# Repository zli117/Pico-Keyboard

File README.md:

# Pico-Keyboard

A hot-swappable mechanical keyboard built from scratch with Pi Pico board, and 3D printed case, with a very configurable firmware. The firmware is in a separate repo: https://github.com/zli117/PicoMK and can be reused for other RP2040 keyboards.

# Pictures

## PCB

## Case

## Build Pictures

# Overall Cost Breakdown

In total per keyboard material cost is roughly $129.57

 * 5 PCB from JLCPCB with shipping: $39.52. Roughly $7.9 per board.
 * 100 hot-swappable PCB socket: $14.50. Used 68, so total $9.86.
 * Pi Pico: $4.99.
 * EC11 Rotary Encoder: $1.10 each.
 * COM-09032 Joystick: $4.50 each.
 * 100 1N4148 diodes: $4.99. Used 70 so $3.50.
 * 150 WS2812B: $14.49. Used 17, so total $1.64.
 * 3D printed case. Each part weight about 50g and there are 5 (2 for plate, and 3 for bottom). Total weight 250g roughly $6.
 * SSD1306 white color: $3 each.
 * GMMK encoder knob: $10.
 * Clear joystick knob: $5.
 * Stabilizers: $16.99 per set.
 * Akko clear translucent keycap: $39.99.
 * Akko blue switch: $9.99 per 45. Used 68, so total $15.10
 
# Build Instructions

## PCB
PCB is designed with KiCAD 6, and everything is under the [PCB](PCB/) folder. Pre-plotted files that can be uploaded to board factory are in 
`Gerber.zip` file. However, different factory may have different plotting settings, so it's recommended to replot with KiCad following factory's instruction. The provided one is for JLCPCB. 

## Case
Case is designed with Fusion 360. The file ends in `.f3z` contains the original Fusion 360 source. My build used SUNLU Clear PLA and is sliced with Cura. I put screw holes on the bottom to secure the PCB, but in practice it's not necessary to screw down the PCB once you've installed switches. So those are optional. The screws between plate and bottom are not optional however.

## Firmware
Firmware is in a separate repo: [PicoMK](https://github.com/zli117/PicoMK). Please see the instruction on how to configure and build the firmware there. 

# PCB Library Licenses

 * Pico symbol, footprint from https://github.com/ncarandini/KiCad-RP-Pico under CC-BY-SA 4.0. 3D model for Pico is obtained from Raspberry Pi Foundation.
 * COM-09032 symbol, footprint and 3D models are from SnapEDA.
 * Key switch footprints and 3D models are from https://github.com/perigoso/keyswitch-kicad-library 
 * Other symbols are from KiCad library which is under CC-BY-SA 4.0 license. 

This work is licensed under a
[Creative Commons Attribution-ShareAlike 4.0 International License][cc-by-sa].

[![CC BY-SA 4.0][cc-by-sa-image]][cc-by-sa]

[cc-by-sa]: http://creativecommons.org/licenses/by-sa/4.0/
[cc-by-sa-image]: https://licensebuttons.net/l/by-sa/4.0/88x31.png
[cc-by-sa-shield]: https://img.shields.io/badge/License-CC%20BY--SA%204.0-lightgrey.svg

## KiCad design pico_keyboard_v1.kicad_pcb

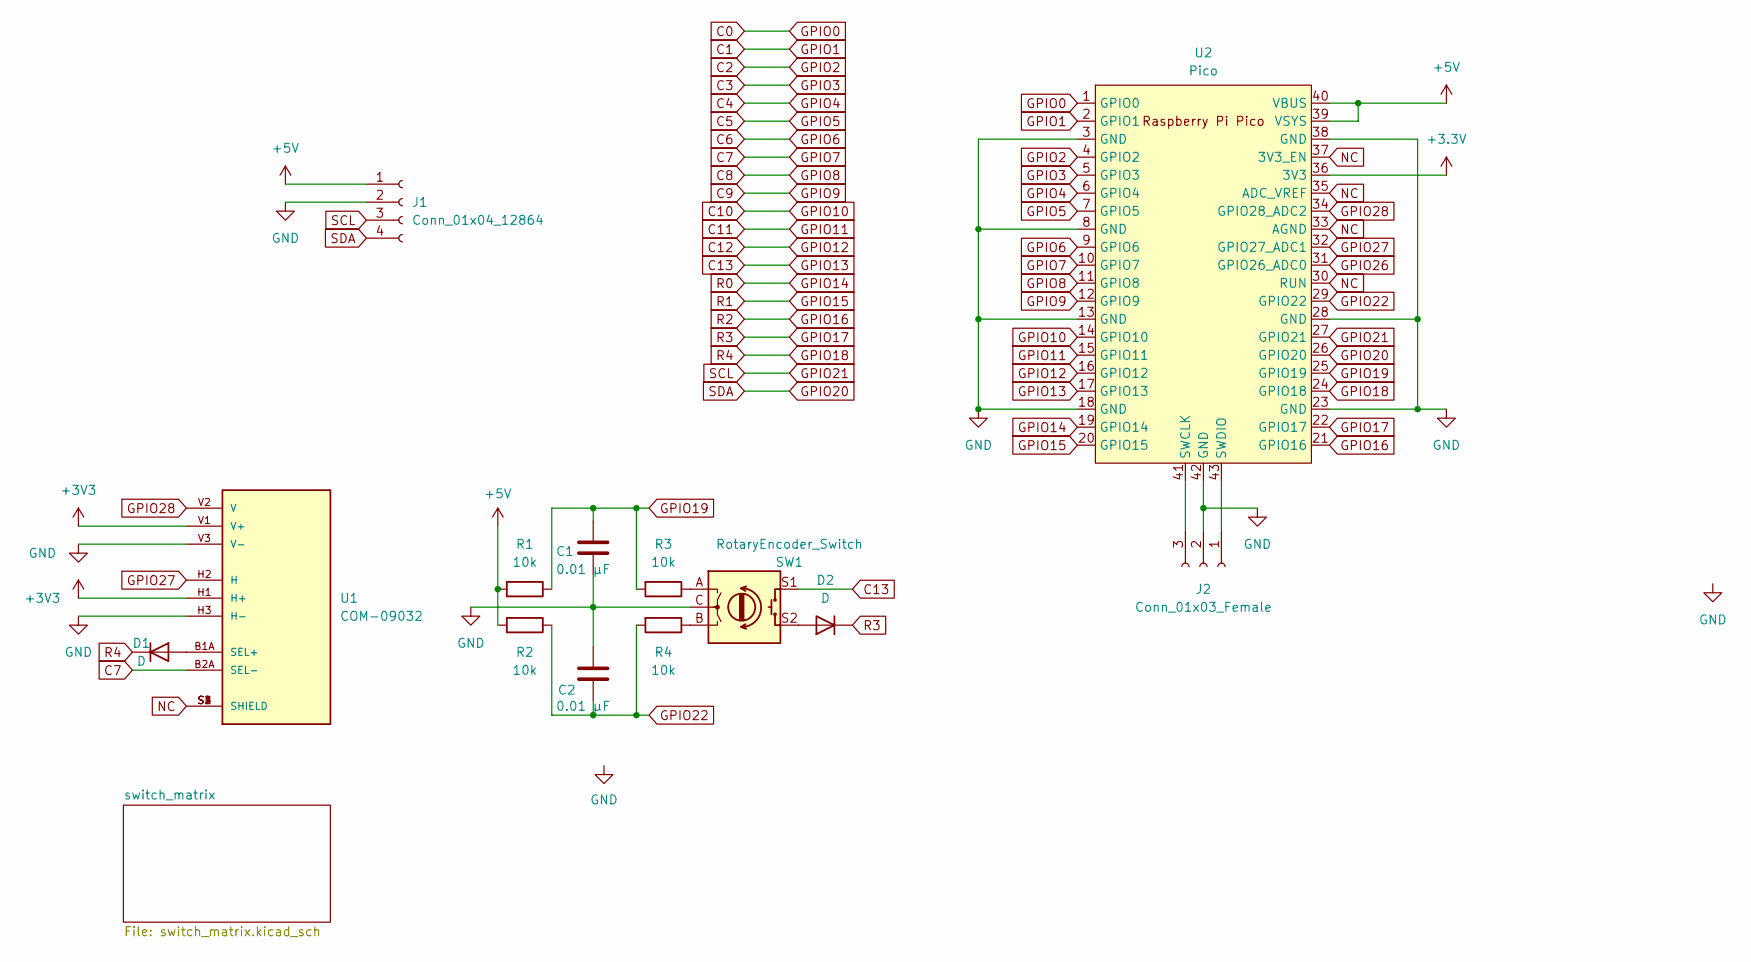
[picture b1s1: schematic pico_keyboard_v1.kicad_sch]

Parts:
C1, C2: 0.01 μF; C_1206_3216Metric_Pad1.33x1.80mm_HandSolder
D1, D2: D; D_DO-35_SOD27_P7.62mm_Horizontal
J1: Conn_01x04_12864; PinHeader_1x04_P2.00mm_Vertical
J2: Conn_01x03_Female; PinHeader_1x03_P2.00mm_Vertical
R1, R2, R3, R4: 10k; R_Axial_DIN0207_L6.3mm_D2.5mm_P10.16mm_Horizontal
SW1: RotaryEncoder_Switch; RotaryEncoder_Alps_EC11E-Switch_Vertical_H20mm_CircularMoun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
U1: COM-09032; XDCR_COM-09032; PARTREV N/A
U2: Pico; RPi_Pico_SMD_TH

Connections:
+5V: J1.1, R1.2, R2.2, U2.39 (VSYS), U2.40 (VBUS)
C0: U2.1 (GPIO0); also elsewhere on the board
C1: U2.2 (GPIO1); also elsewhere on the board
C2: U2.4 (GPIO2); also elsewhere on the board
C3: U2.5 (GPIO3); also elsewhere on the board
C4: U2.6 (GPIO4); also elsewhere on the board
C5: U2.7 (GPIO5); also elsewhere on the board
C6: U2.9 (GPIO6); also elsewhere on the board
C7: U1.B2A (SEL-), U2.10 (GPIO7); also elsewhere on the board
C8: U2.11 (GPIO8); also elsewhere on the board
C9: U2.12 (GPIO9); also elsewhere on the board
C10: U2.14 (GPIO10); also elsewhere on the board
C11: U2.15 (GPIO11); also elsewhere on the board
C12: U2.16 (GPIO12); also elsewhere on the board
C13: SW1.S1, U2.17 (GPIO13); also elsewhere on the board
GND: C1.2, C2.1, J1.2, J2.2, SW1.C, U1.H3 (H-), U1.V3 (V-), U2.3 (GND), U2.8 (GND), U2.13 (GND), U2.18 (GND), U2.23 (GND), U2.28 (GND), U2.38 (GND), U2.42 (GND)
GPIO14: U2.19 (GPIO14); also elsewhere on the board
GPIO15: U2.20 (GPIO15); also elsewhere on the board
GPIO16: U2.21 (GPIO16); also elsewhere on the board
GPIO17: D2.1 (K), U2.22 (GPIO17); also elsewhere on the board
GPIO18: D1.1 (K), U2.24 (GPIO18); also elsewhere on the board
GPIO19: C1.1, R1.1, R3.2, U2.25 (GPIO19)
GPIO20: J1.4, U2.26 (GPIO20)
GPIO21: J1.3, U2.27 (GPIO21)
GPIO22: C2.2, R2.1, R4.2, U2.29 (GPIO22)
GPIO26: U2.31 (GPIO26_ADC0)
GPIO27: U1.H2 (H), U2.32 (GPIO27_ADC1)
GPIO28: U1.V2 (V), U2.34 (GPIO28_ADC2)
NC: U1.S1 (SHIELD), U1.S2 (SHIELD), U1.S3 (SHIELD), U1.S4 (SHIELD), U2.30 (RUN), U2.33 (AGND), U2.35 (ADC_VREF), U2.37 (3V3_EN)
unnamed: D1.2 (A), U1.B1A (SEL+)
unnamed: D2.2 (A), SW1.S2
unnamed: J2.1, U2.43 (SWDIO)
unnamed: J2.3, U2.41 (SWCLK)
unnamed: R3.1, SW1.A
unnamed: R4.1, SW1.B

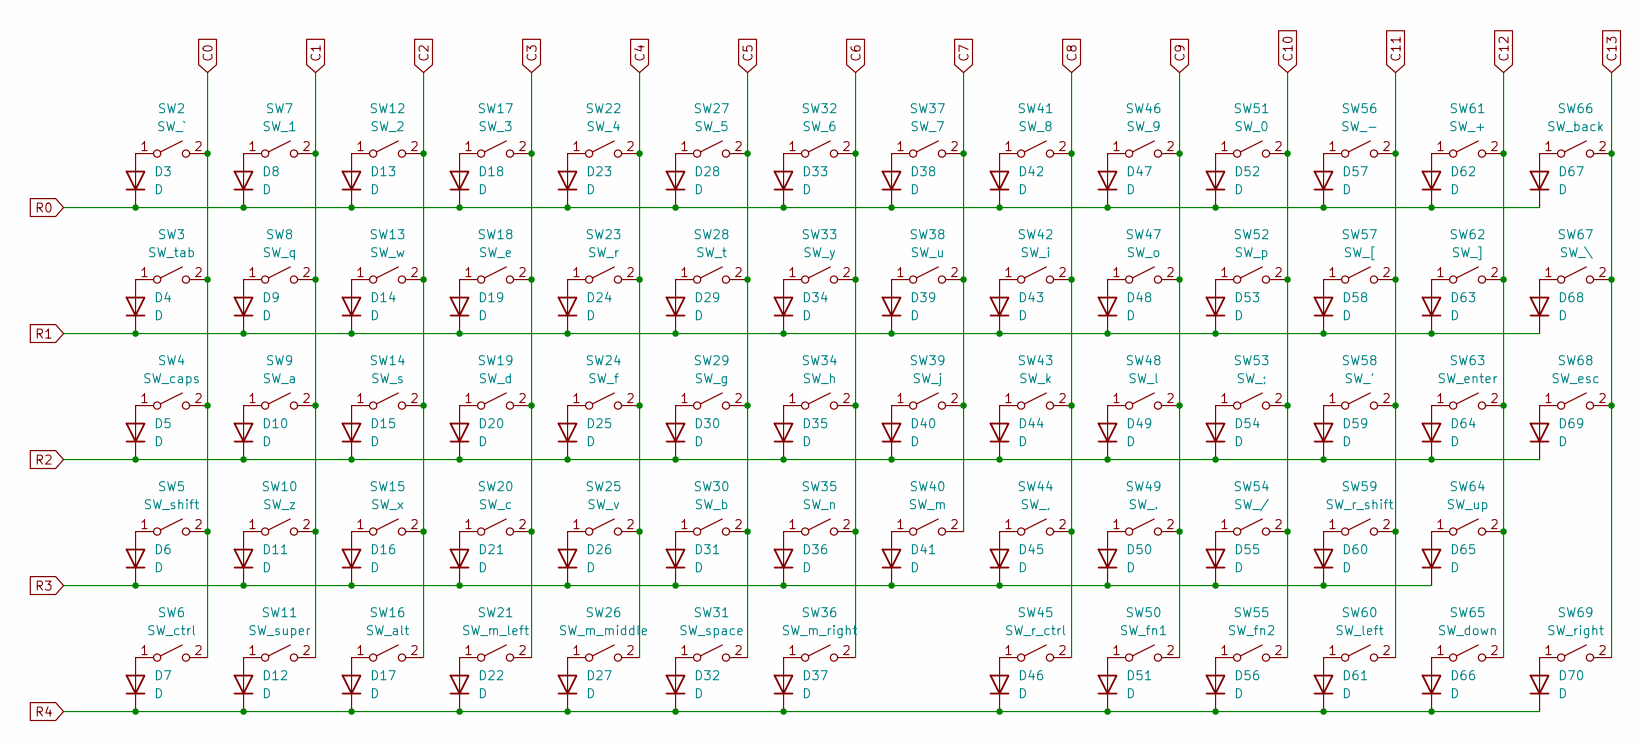
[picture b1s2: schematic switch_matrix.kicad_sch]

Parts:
D3, D4, D5, D6, D7, D8, D9, D10, D11, D12, D13, D14, D15, D16, D17, D18, D19, D20, D21, D22, D23, D24, D25, D26, D27, D28, D29, D30, D31, D32, D33, D34, D35, D36, D37, D38, D39, D40, D41, D42, D43, D44, D45, D46, D47, D48, D49, D50, D51, D52, D53, D54, D55, D56, D57, D58, D59, D60, D61, D62, D63, D64, D65, D66, D67, D68, D69, D70: D; D_DO-35_SOD27_P7.62mm_Horizontal
SW2: SW_`; SW_Hotswap_Kailh_MX_1.00u
SW3: SW_tab; SW_Hotswap_Kailh_MX_1.50u
SW4: SW_caps; SW_Hotswap_Kailh_MX_1.75u
SW5: SW_shift; SW_Hotswap_Kailh_MX_2.25u
SW6: SW_ctrl; SW_Hotswap_Kailh_MX_1.25u
SW7: SW_1; SW_Hotswap_Kailh_MX_1.00u
SW8: SW_q; SW_Hotswap_Kailh_MX_1.00u
SW9: SW_a; SW_Hotswap_Kailh_MX_1.00u
SW10: SW_z; SW_Hotswap_Kailh_MX_1.00u
SW11: SW_super; SW_Hotswap_Kailh_MX_1.25u
SW12: SW_2; SW_Hotswap_Kailh_MX_1.00u
SW13: SW_w; SW_Hotswap_Kailh_MX_1.00u
SW14: SW_s; SW_Hotswap_Kailh_MX_1.00u
SW15: SW_x; SW_Hotswap_Kailh_MX_1.00u
SW16: SW_alt; SW_Hotswap_Kailh_MX_1.25u
SW17: SW_3; SW_Hotswap_Kailh_MX_1.00u
SW18: SW_e; SW_Hotswap_Kailh_MX_1.00u
SW19: SW_d; SW_Hotswap_Kailh_MX_1.00u
SW20: SW_c; SW_Hotswap_Kailh_MX_1.00u
SW21: SW_m_left; SW_Hotswap_Kailh_MX_1.00u
SW22: SW_4; SW_Hotswap_Kailh_MX_1.00u
SW23: SW_r; SW_Hotswap_Kailh_MX_1.00u
SW24: SW_f; SW_Hotswap_Kailh_MX_1.00u
SW25: SW_v; SW_Hotswap_Kailh_MX_1.00u
SW26: SW_m_middle; SW_Hotswap_Kailh_MX_1.00u
SW27: SW_5; SW_Hotswap_Kailh_MX_1.00u
SW28: SW_t; SW_Hotswap_Kailh_MX_1.00u
SW29: SW_g; SW_Hotswap_Kailh_MX_1.00u
SW30: SW_b; SW_Hotswap_Kailh_MX_1.00u
SW31: SW_space; SW_Hotswap_Kailh_MX_6.25u
SW32: SW_6; SW_Hotswap_Kailh_MX_1.00u
SW33: SW_y; SW_Hotswap_Kailh_MX_1.00u
SW34: SW_h; SW_Hotswap_Kailh_MX_1.00u
SW35: SW_n; SW_Hotswap_Kailh_MX_1.00u
SW36: SW_m_right; SW_Hotswap_Kailh_MX_1.00u
SW37: SW_7; SW_Hotswap_Kailh_MX_1.00u
SW38: SW_u; SW_Hotswap_Kailh_MX_1.00u
SW39: SW_j; SW_Hotswap_Kailh_MX_1.00u
SW40: SW_m; SW_Hotswap_Kailh_MX_1.00u
SW41: SW_8; SW_Hotswap_Kailh_MX_1.00u
SW42: SW_i; SW_Hotswap_Kailh_MX_1.00u
SW43: SW_k; SW_Hotswap_Kailh_MX_1.00u
SW44: SW_,; SW_Hotswap_Kailh_MX_1.00u
SW45: SW_r_ctrl; SW_Hotswap_Kailh_MX_1.00u
SW46: SW_9; SW_Hotswap_Kailh_MX_1.00u
SW47: SW_o; SW_Hotswap_Kailh_MX_1.00u
SW48: SW_l; SW_Hotswap_Kailh_MX_1.00u
SW49: SW_.; SW_Hotswap_Kailh_MX_1.00u
SW50: SW_fn1; SW_Hotswap_Kailh_MX_1.00u
SW51: SW_0; SW_Hotswap_Kailh_MX_1.00u
SW52: SW_p; SW_Hotswap_Kailh_MX_1.00u
SW53: SW_;; SW_Hotswap_Kailh_MX_1.00u
SW54: SW_/; SW_Hotswap_Kailh_MX_1.00u
SW55: SW_fn2; SW_Hotswap_Kailh_MX_1.00u
SW56: SW_-; SW_Hotswap_Kailh_MX_1.00u
SW57: SW_[; SW_Hotswap_Kailh_MX_1.00u
SW58: SW_'; SW_Hotswap_Kailh_MX_1.00u
SW59: SW_r_shift; SW_Hotswap_Kailh_MX_1.75u
SW60: SW_left; SW_Hotswap_Kailh_MX_1.00u
SW61: SW_+; SW_Hotswap_Kailh_MX_1.00u
SW62: SW_]; SW_Hotswap_Kailh_MX_1.00u
SW63: SW_enter; SW_Hotswap_Kailh_MX_2.25u
SW64: SW_up; SW_Hotswap_Kailh_MX_1.00u
SW65: SW_down; SW_Hotswap_Kailh_MX_1.00u
SW66: SW_back; SW_Hotswap_Kailh_MX_2.00u
SW67: SW_\; SW_Hotswap_Kailh_MX_1.00u
SW68: SW_esc; SW_Hotswap_Kailh_MX_1.00u
SW69: SW_right; SW_Hotswap_Kailh_MX_1.00u

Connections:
C0: SW2.2 (B), SW3.2 (B), SW4.2 (B), SW5.2 (B), SW6.2 (B); also elsewhere on the board
C1: SW7.2 (B), SW8.2 (B), SW9.2 (B), SW10.2 (B), SW11.2 (B); also elsewhere on the board
C2: SW12.2 (B), SW13.2 (B), SW14.2 (B), SW15.2 (B), SW16.2 (B); also elsewhere on the board
C3: SW17.2 (B), SW18.2 (B), SW19.2 (B), SW20.2 (B), SW21.2 (B); also elsewhere on the board
C4: SW22.2 (B), SW23.2 (B), SW24.2 (B), SW25.2 (B), SW26.2 (B); also elsewhere on the board
C5: SW27.2 (B), SW28.2 (B), SW29.2 (B), SW30.2 (B), SW31.2 (B); also elsewhere on the board
C6: SW32.2 (B), SW33.2 (B), SW34.2 (B), SW35.2 (B), SW36.2 (B); also elsewhere on the board
C7: SW37.2 (B), SW38.2 (B), SW39.2 (B), SW40.2 (B); also elsewhere on the board
C8: SW41.2 (B), SW42.2 (B), SW43.2 (B), SW44.2 (B), SW45.2 (B); also elsewhere on the board
C9: SW46.2 (B), SW47.2 (B), SW48.2 (B), SW49.2 (B), SW50.2 (B); also elsewhere on the board
C10: SW51.2 (B), SW52.2 (B), SW53.2 (B), SW54.2 (B), SW55.2 (B); also elsewhere on the board
C11: SW56.2 (B), SW57.2 (B), SW58.2 (B), SW59.2 (B), SW60.2 (B); also elsewhere on the board
C12: SW61.2 (B), SW62.2 (B), SW63.2 (B), SW64.2 (B), SW65.2 (B); also elsewhere on the board
C13: SW66.2 (B), SW67.2 (B), SW68.2 (B), SW69.2 (B); also elsewhere on the board
GPIO14: D3.1 (K), D8.1 (K), D13.1 (K), D18.1 (K), D23.1 (K), D28.1 (K), D33.1 (K), D38.1 (K), D42.1 (K), D47.1 (K), D52.1 (K), D57.1 (K), D62.1 (K), D67.1 (K); also elsewhere on the board
GPIO15: D4.1 (K), D9.1 (K), D14.1 (K), D19.1 (K), D24.1 (K), D29.1 (K), D34.1 (K), D39.1 (K), D43.1 (K), D48.1 (K), D53.1 (K), D58.1 (K), D63.1 (K), D68.1 (K); also elsewhere on the board
GPIO16: D5.1 (K), D10.1 (K), D15.1 (K), D20.1 (K), D25.1 (K), D30.1 (K), D35.1 (K), D40.1 (K), D44.1 (K), D49.1 (K), D54.1 (K), D59.1 (K), D64.1 (K), D69.1 (K); also elsewhere on the board
GPIO17: D6.1 (K), D11.1 (K), D16.1 (K), D21.1 (K), D26.1 (K), D31.1 (K), D36.1 (K), D41.1 (K), D45.1 (K), D50.1 (K), D55.1 (K), D60.1 (K), D65.1 (K); also elsewhere on the board
GPIO18: D7.1 (K), D12.1 (K), D17.1 (K), D22.1 (K), D27.1 (K), D32.1 (K), D37.1 (K), D46.1 (K), D51.1 (K), D56.1 (K), D61.1 (K), D66.1 (K), D70.1 (K); also elsewhere on the board
unnamed: D3.2 (A), SW2.1 (A)
unnamed: D4.2 (A), SW3.1 (A)
unnamed: D5.2 (A), SW4.1 (A)
unnamed: D6.2 (A), SW5.1 (A)
unnamed: D7.2 (A), SW6.1 (A)
unnamed: D8.2 (A), SW7.1 (A)
unnamed: D9.2 (A), SW8.1 (A)
unnamed: D10.2 (A), SW9.1 (A)
unnamed: D11.2 (A), SW10.1 (A)
unnamed: D12.2 (A), SW11.1 (A)
unnamed: D13.2 (A), SW12.1 (A)
unnamed: D14.2 (A), SW13.1 (A)
unnamed: D15.2 (A), SW14.1 (A)
unnamed: D16.2 (A), SW15.1 (A)
unnamed: D17.2 (A), SW16.1 (A)
unnamed: D18.2 (A), SW17.1 (A)
unnamed: D19.2 (A), SW18.1 (A)
unnamed: D20.2 (A), SW19.1 (A)
unnamed: D21.2 (A), SW20.1 (A)
unnamed: D22.2 (A), SW21.1 (A)
unnamed: D23.2 (A), SW22.1 (A)
unnamed: D24.2 (A), SW23.1 (A)
unnamed: D25.2 (A), SW24.1 (A)
unnamed: D26.2 (A), SW25.1 (A)
unnamed: D27.2 (A), SW26.1 (A)
unnamed: D28.2 (A), SW27.1 (A)
unnamed: D29.2 (A), SW28.1 (A)
unnamed: D30.2 (A), SW29.1 (A)
unnamed: D31.2 (A), SW30.1 (A)
unnamed: D32.2 (A), SW31.1 (A)
unnamed: D33.2 (A), SW32.1 (A)
unnamed: D34.2 (A), SW33.1 (A)
unnamed: D35.2 (A), SW34.1 (A)
unnamed: D36.2 (A), SW35.1 (A)
unnamed: D37.2 (A), SW36.1 (A)
unnamed: D38.2 (A), SW37.1 (A)
unnamed: D39.2 (A), SW38.1 (A)
unnamed: D40.2 (A), SW39.1 (A)
unnamed: D41.2 (A), SW40.1 (A)
unnamed: D42.2 (A), SW41.1 (A)
unnamed: D43.2 (A), SW42.1 (A)
unnamed: D44.2 (A), SW43.1 (A)
unnamed: D45.2 (A), SW44.1 (A)
unnamed: D46.2 (A), SW45.1 (A)
unnamed: D47.2 (A), SW46.1 (A)
unnamed: D48.2 (A), SW47.1 (A)
unnamed: D49.2 (A), SW48.1 (A)
unnamed: D50.2 (A), SW49.1 (A)
unnamed: D51.2 (A), SW50.1 (A)
unnamed: D52.2 (A), SW51.1 (A)
unnamed: D53.2 (A), SW52.1 (A)
unnamed: D54.2 (A), SW53.1 (A)
unnamed: D55.2 (A), SW54.1 (A)
unnamed: D56.2 (A), SW55.1 (A)
unnamed: D57.2 (A), SW56.1 (A)
unnamed: D58.2 (A), SW57.1 (A)
unnamed: D59.2 (A), SW58.1 (A)
unnamed: D60.2 (A), SW59.1 (A)
unnamed: D61.2 (A), SW60.1 (A)
unnamed: D62.2 (A), SW61.1 (A)
unnamed: D63.2 (A), SW62.1 (A)
unnamed: D64.2 (A), SW63.1 (A)
unnamed: D65.2 (A), SW64.1 (A)
unnamed: D66.2 (A), SW65.1 (A)
unnamed: D67.2 (A), SW66.1 (A)
unnamed: D68.2 (A), SW67.1 (A)
unnamed: D69.2 (A), SW68.1 (A)
unnamed: D70.2 (A), SW69.1 (A)

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
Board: 2 copper layers, 149 parts (0 on the bottom side), 103 nets, no tracks yet.

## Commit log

2022-05-29 More changes
2022-05-29 Draft
2022-05-30 More polished. Added mounting hole and led
2022-05-30 Moved diode text to back
2022-05-30 Rounded corner
2022-05-30 Good enough
2022-05-30 V1, before a major change
2022-05-31 New version
2022-05-31 Rounded corners
2022-06-01 V0.2. Before another major redesign
2022-06-02 Updated edge cut layer
2022-06-02 Added library
2022-06-02 Removed plot
2022-06-02 Added some logos
2022-06-02 Changed github repo name
2022-06-02 Added some images
2022-06-02 Centered on the worksheet
2022-06-12 Changed layout a bit. Starting of V0.4
2022-06-12 More minor changes
2022-06-12 Plotted
2022-06-12 New plots
2022-06-12 Updated the location of a silkscreen
2022-06-21 Removed unused library
2022-06-21 Moved project to PCB dir
2022-06-21 Updated pcb images
2022-06-21 Added license information for pcb libraries
2022-06-26 Updated 3d model and gerber
2022-06-26 Added license
2022-06-26 Fixing some 3d model dimension issues
2022-06-27 Renamed dir
2022-06-28 Updated case model to hopefully fix the connector issues
2022-07-02 Fixed the RC filter for rotary encoder
2022-07-02 Changed the routing a bit
2022-10-16 Started working on v0.5
2022-10-17 Updated pico footprint to remove warnings
2022-10-17 Use both types of joystick
2022-10-31 Added some things

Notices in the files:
PCB/switch_matrix.kicad_sch:
CC BY-SA 2.0
